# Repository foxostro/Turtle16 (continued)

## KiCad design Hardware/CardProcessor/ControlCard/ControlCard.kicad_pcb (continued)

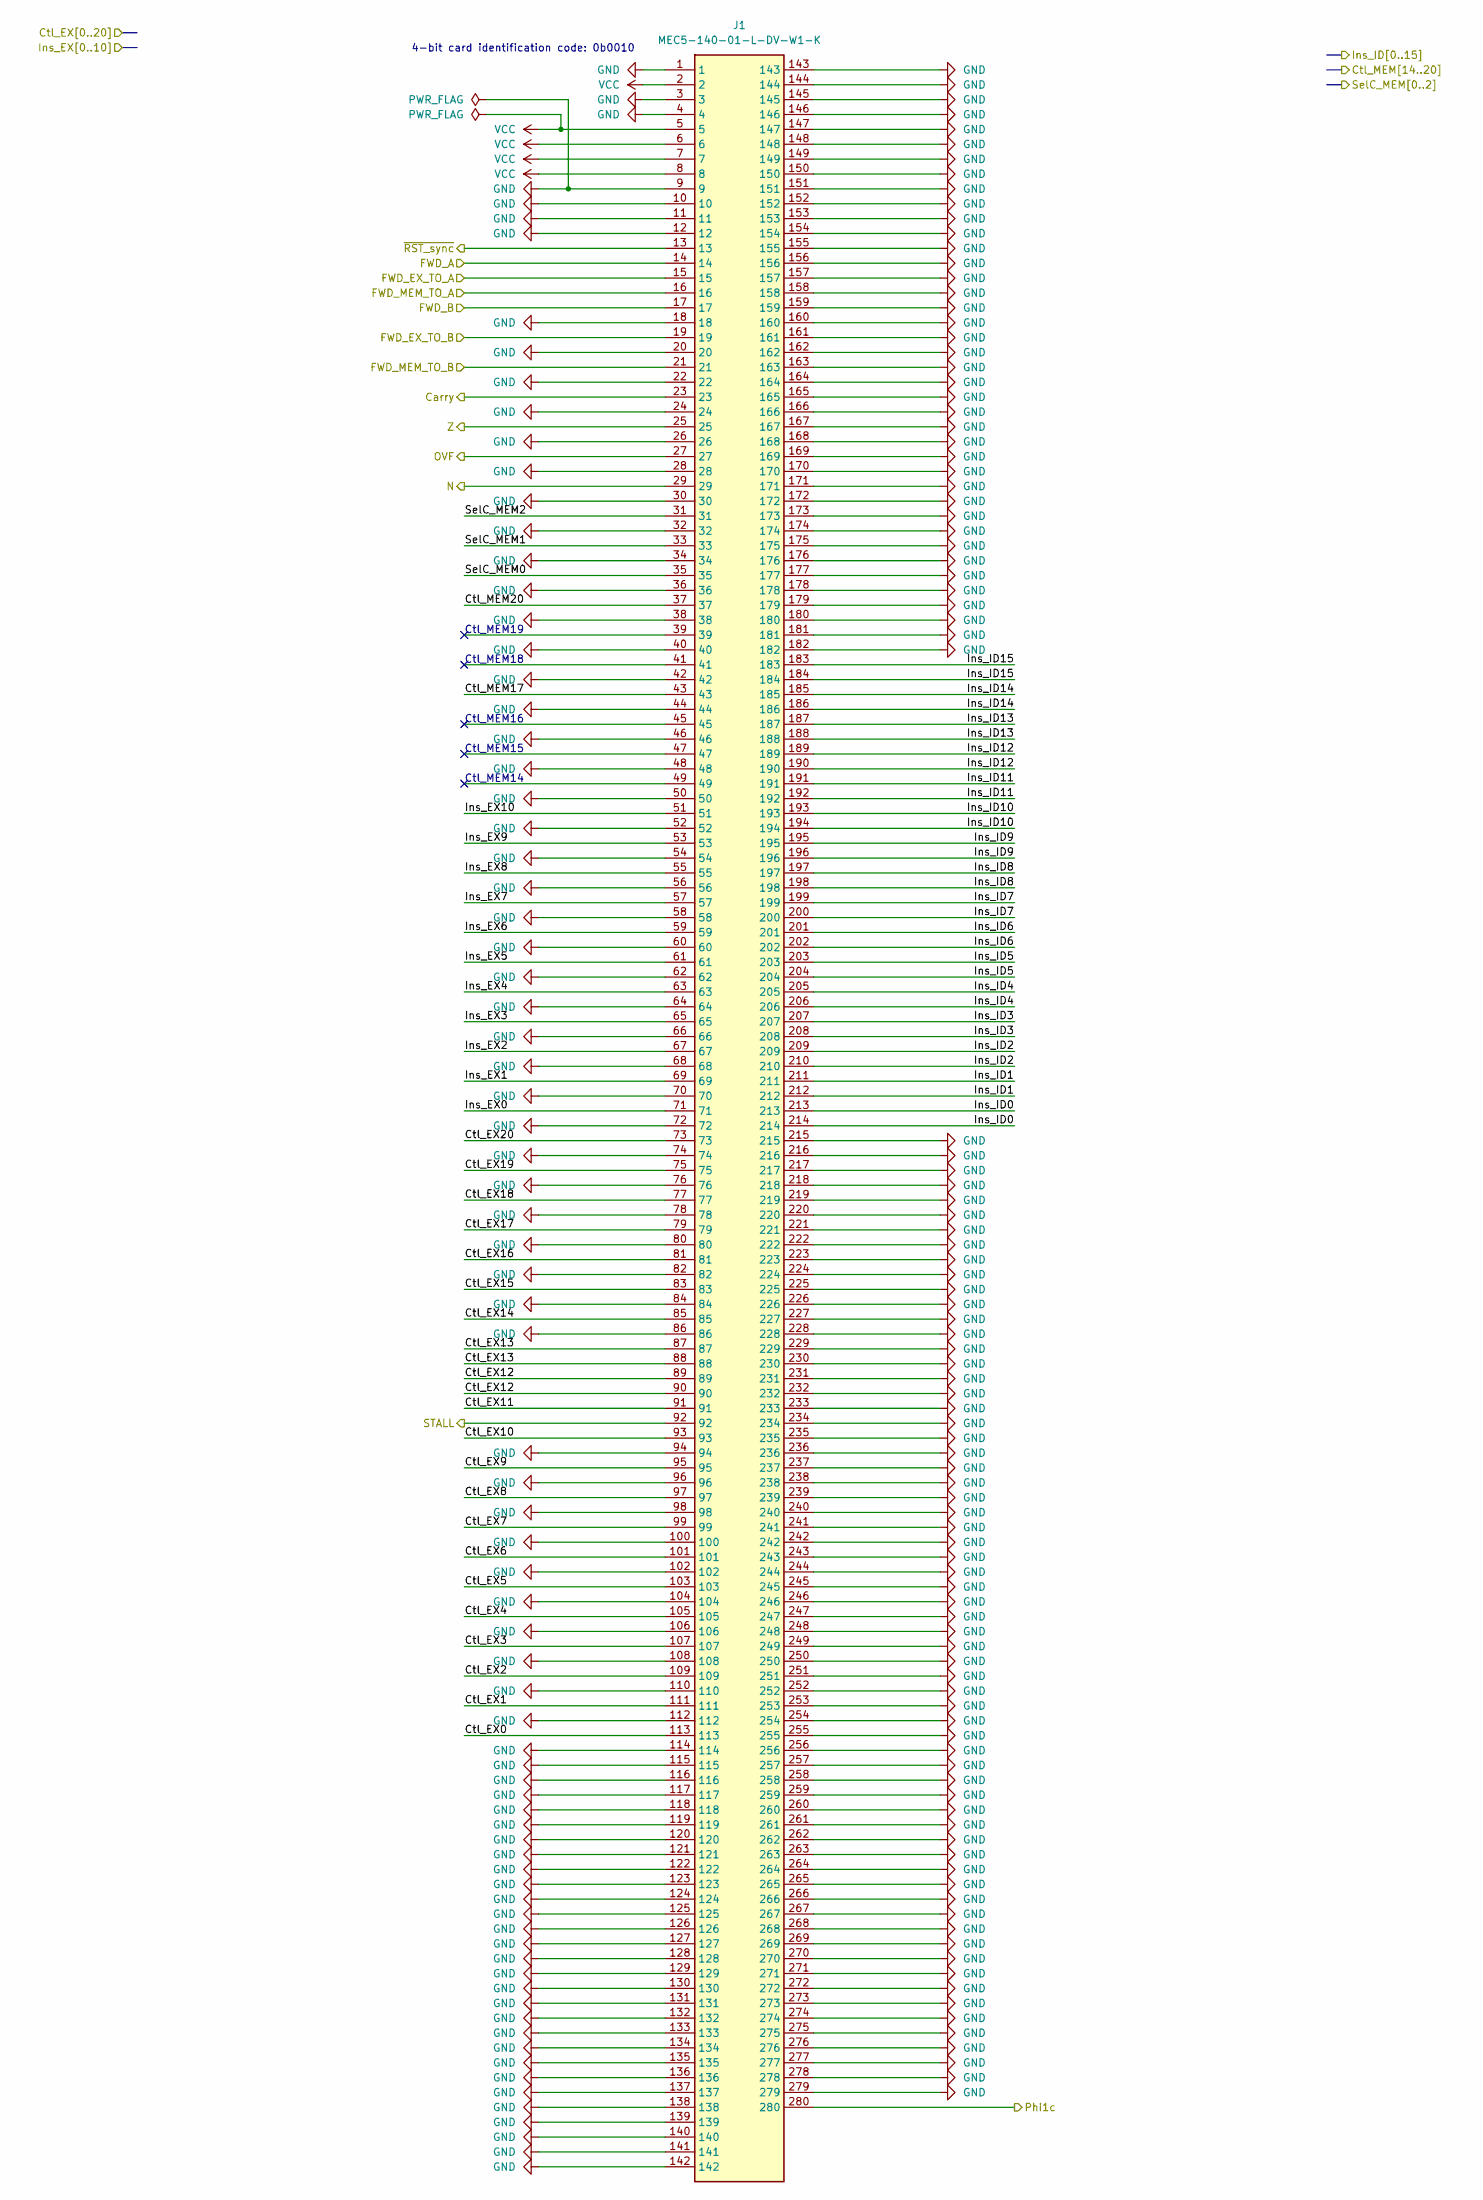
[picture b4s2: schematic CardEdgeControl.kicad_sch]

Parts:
J1: MEC5-140-01-L-DV-W1-K; MEC5-140-01-L-DV-W1-K_Edge; Mouser Part Number 200-MEC514001LDVW1K

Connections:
/CardEdgeControl/Carry: J1.23; also elsewhere on the board
/CardEdgeControl/Ctl_MEM17: J1.43; also elsewhere on the board
/CardEdgeControl/Ctl_MEM20: J1.37; also elsewhere on the board
/CardEdgeControl/FWD_A: J1.14; also elsewhere on the board
/CardEdgeControl/FWD_B: J1.17; also elsewhere on the board
/CardEdgeControl/FWD_EX_TO_A: J1.15; also elsewhere on the board
/CardEdgeControl/FWD_EX_TO_B: J1.19; also elsewhere on the board
/CardEdgeControl/FWD_MEM_TO_A: J1.16; also elsewhere on the board
/CardEdgeControl/FWD_MEM_TO_B: J1.21; also elsewhere on the board
/CardEdgeControl/Ins_ID0: J1.213, J1.214; also elsewhere on the board
/CardEdgeControl/Ins_ID1: J1.211, J1.212; also elsewhere on the board
/CardEdgeControl/Ins_ID2: J1.209, J1.210; also elsewhere on the board
/CardEdgeControl/Ins_ID3: J1.207, J1.208; also elsewhere on the board
/CardEdgeControl/Ins_ID4: J1.205, J1.206; also elsewhere on the board
/CardEdgeControl/Ins_ID5: J1.203, J1.204; also elsewhere on the board
/CardEdgeControl/Ins_ID6: J1.201, J1.202; also elsewhere on the board
/CardEdgeControl/Ins_ID7: J1.199, J1.200; also elsewhere on the board
/CardEdgeControl/Ins_ID8: J1.197, J1.198; also elsewhere on the board
/CardEdgeControl/Ins_ID9: J1.195, J1.196; also elsewhere on the board
/CardEdgeControl/Ins_ID10: J1.193, J1.194; also elsewhere on the board
/CardEdgeControl/Ins_ID11: J1.191, J1.192; also elsewhere on the board
/CardEdgeControl/Ins_ID12: J1.189, J1.190; also elsewhere on the board
/CardEdgeControl/Ins_ID13: J1.187, J1.188; also elsewhere on the board
/CardEdgeControl/Ins_ID14: J1.185, J1.186; also elsewhere on the board
/CardEdgeControl/Ins_ID15: J1.183, J1.184; also elsewhere on the board
/CardEdgeControl/N: J1.29; also elsewhere on the board
/CardEdgeControl/OVF: J1.27; also elsewhere on the board
/CardEdgeControl/Phi1c: J1.280; also elsewhere on the board
/CardEdgeControl/SelC_MEM0: J1.35; also elsewhere on the board
/CardEdgeControl/SelC_MEM1: J1.33; also elsewhere on the board
/CardEdgeControl/SelC_MEM2: J1.31; also elsewhere on the board
/CardEdgeControl/Z: J1.25; also elsewhere on the board
/CardEdgeControl/~RST_sync: J1.13; also elsewhere on the board
/ID/Ctl_EX0: J1.113; also elsewhere on the board
/ID/Ctl_EX1: J1.111; also elsewhere on the board
/ID/Ctl_EX2: J1.109; also elsewhere on the board
/ID/Ctl_EX3: J1.107; also elsewhere on the board
/ID/Ctl_EX4: J1.105; also elsewhere on the board
/ID/Ctl_EX5: J1.103; also elsewhere on the board
/ID/Ctl_EX6: J1.101; also elsewhere on the board
/ID/Ctl_EX7: J1.99; also elsewhere on the board
/ID/Ctl_EX8: J1.97; also elsewhere on the board
/ID/Ctl_EX9: J1.95; also elsewhere on the board
/ID/Ctl_EX10: J1.93; also elsewhere on the board
/ID/Ctl_EX11: J1.91; also elsewhere on the board
/ID/Ctl_EX12: J1.89, J1.90; also elsewhere on the board
/ID/Ctl_EX13: J1.87, J1.88; also elsewhere on the board
/ID/Ctl_EX14: J1.85; also elsewhere on the board
/ID/Ctl_EX15: J1.83; also elsewhere on the board
/ID/Ctl_EX16: J1.81; also elsewhere on the board
/ID/Ctl_EX17: J1.79; also elsewhere on the board
/ID/Ctl_EX18: J1.77; also elsewhere on the board
/ID/Ctl_EX19: J1.75; also elsewhere on the board
/ID/Ctl_EX20: J1.73; also elsewhere on the board
/ID/Hazard Control/STALL: J1.92; also elsewhere on the board
/ID/Ins_EX0: J1.71; also elsewhere on the board
/ID/Ins_EX1: J1.69; also elsewhere on the board
/ID/Ins_EX2: J1.67; also elsewhere on the board
/ID/Ins_EX3: J1.65; also elsewhere on the board
/ID/Ins_EX4: J1.63; also elsewhere on the board
/ID/Ins_EX5: J1.61; also elsewhere on the board
/ID/Ins_EX6: J1.59; also elsewhere on the board
/ID/Ins_EX7: J1.57; also elsewhere on the board
/ID/Ins_EX8: J1.55; also elsewhere on the board
/ID/Ins_EX9: J1.53; also elsewhere on the board
/ID/Ins_EX10: J1.51; also elsewhere on the board
GND: J1.1, J1.3, J1.4, J1.9, J1.10, J1.11, J1.12, J1.18, J1.20, J1.22, J1.24, J1.26, J1.28, J1.30, J1.32, J1.34, J1.36, J1.38, J1.40, J1.42, J1.44, J1.46, J1.48, J1.50, J1.52, J1.54, J1.56, J1.58, J1.60, J1.62, J1.64, J1.66, J1.68, J1.70, J1.72, J1.74, J1.76, J1.78, J1.80, J1.82, J1.84, J1.86, J1.94, J1.96, J1.98, J1.100, J1.102, J1.104, J1.106, J1.108, J1.110, J1.112, J1.114, J1.115, J1.116, J1.117, J1.118, J1.119, J1.120, J1.121, J1.122, J1.123, J1.124, J1.125, J1.126, J1.127, J1.128, J1.129, J1.130, J1.131, J1.132, J1.133, J1.134, J1.135, J1.136, J1.137, J1.138, J1.139, J1.140, J1.141, J1.142, J1.143, J1.144, J1.145, J1.146, J1.147, J1.148, J1.149, J1.150, J1.151, J1.152, J1.153, J1.154, J1.155, J1.156, J1.157, J1.158, J1.159, J1.160, J1.161, J1.162, J1.163, J1.164, J1.165, J1.166, J1.167, J1.168, J1.169, J1.170, J1.171, J1.172, J1.173, J1.174, J1.175, J1.176, J1.177, J1.178, J1.179, J1.180, J1.181, J1.182, J1.215, J1.216, J1.217, J1.218, J1.219, J1.220, J1.221, J1.222, J1.223, J1.224, J1.225, J1.226, J1.227, J1.228, J1.229, J1.230, J1.231, J1.232, J1.233, J1.234, J1.235, J1.236, J1.237, J1.238, J1.239, J1.240, J1.241, J1.242, J1.243, J1.244, J1.245, J1.246, J1.247, J1.248, J1.249, J1.250, J1.251, J1.252, J1.253, J1.254, J1.255, J1.256, J1.257, J1.258, J1.259, J1.260, J1.261, J1.262, J1.263, J1.264, J1.265, J1.266, J1.267, J1.268, J1.269, J1.270, J1.271, J1.272, J1.273, J1.274, J1.275, J1.276, J1.277, J1.278, J1.279; also elsewhere on the board
VCC: J1.2, J1.5, J1.6, J1.7, J1.8; also elsewhere on the board

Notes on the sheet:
Ctl_MEM16
4-bit card identification code: 0b0010
Ctl_MEM15
Ctl_MEM19
Ctl_MEM18
Ctl_MEM14

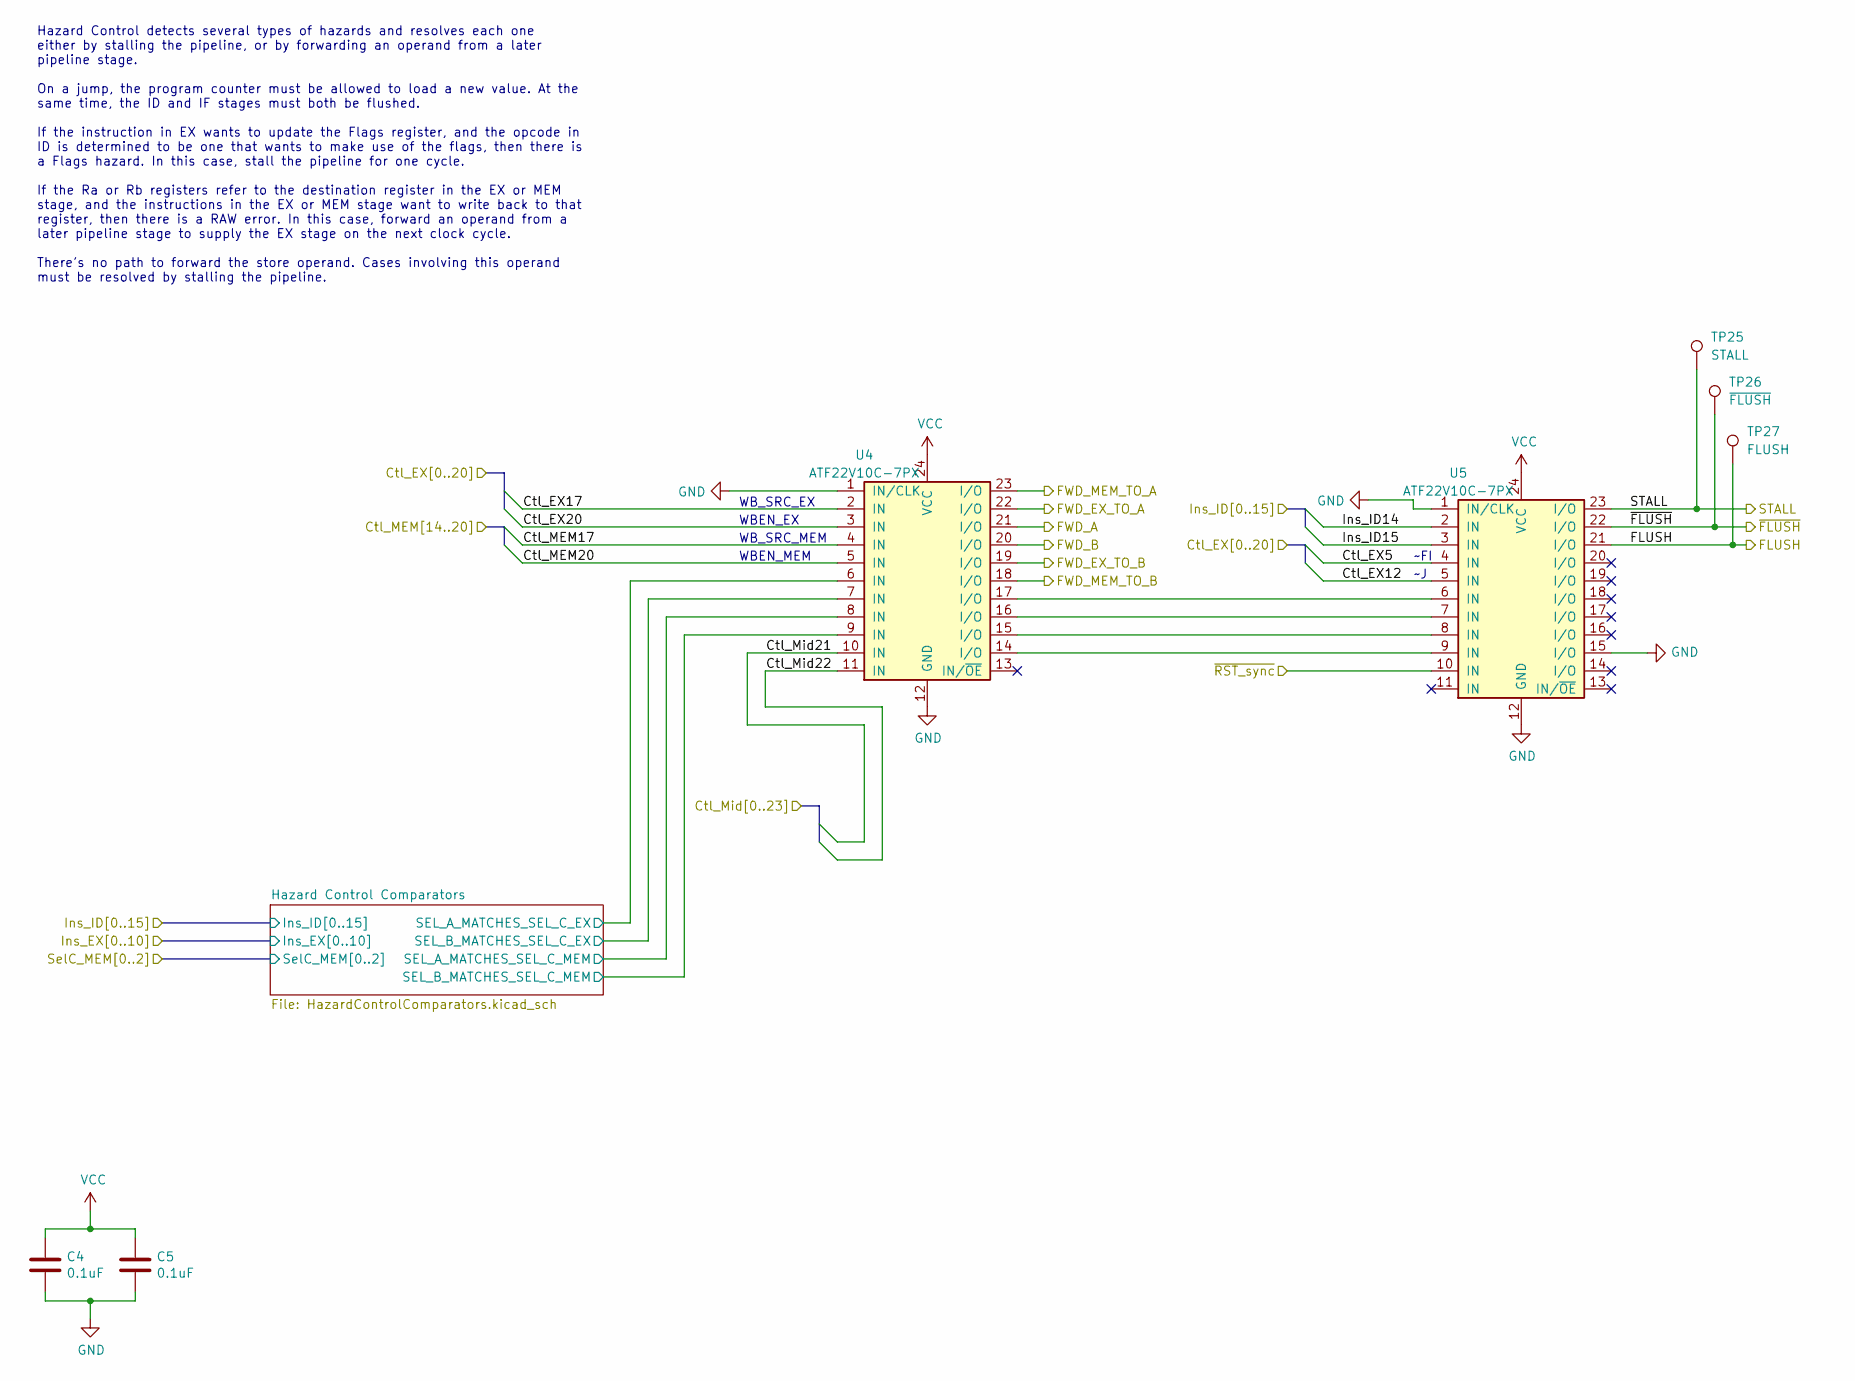
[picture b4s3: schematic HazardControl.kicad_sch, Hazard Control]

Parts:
C4, C5: 0.1uF; C_0603_1608Metric; Manufacturer# EMK107B7104KAHT; Mouser# 963-EMK107B7104KAHT
TP25: STALL; TestPoint_Pad_D1.0mm
TP26: ~{FLUSH}; TestPoint_Pad_D1.0mm
TP27: FLUSH; TestPoint_Pad_D1.0mm
U4, U5: ATF22V10C-7PX; DIP-24_W7.62mm_Socket; Manufacturer# ATF22V10C-7PX; Mouser# 556-AF22V10C7PX

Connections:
/CardEdgeControl/Ctl_MEM17: U4.4 (IN); also elsewhere on the board
/CardEdgeControl/Ctl_MEM20: U4.5 (IN); also elsewhere on the board
/CardEdgeControl/FWD_A: U4.21 (I/O); also elsewhere on the board
/CardEdgeControl/FWD_B: U4.20 (I/O); also elsewhere on the board
/CardEdgeControl/FWD_EX_TO_A: U4.22 (I/O); also elsewhere on the board
/CardEdgeControl/FWD_EX_TO_B: U4.19 (I/O); also elsewhere on the board
/CardEdgeControl/FWD_MEM_TO_A: U4.23 (I/O); also elsewhere on the board
/CardEdgeControl/FWD_MEM_TO_B: U4.18 (I/O); also elsewhere on the board
/CardEdgeControl/Ins_ID14: U5.2 (IN); also elsewhere on the board
/CardEdgeControl/Ins_ID15: U5.3 (IN); also elsewhere on the board
/CardEdgeControl/~RST_sync: U5.10 (IN); also elsewhere on the board
/ID/Ctl_EX5: U5.4 (IN); also elsewhere on the board
/ID/Ctl_EX12: U5.5 (IN); also elsewhere on the board
/ID/Ctl_EX17: U4.2 (IN); also elsewhere on the board
/ID/Ctl_EX20: U4.3 (IN); also elsewhere on the board
/ID/Ctl_Mid21: U4.10 (IN); also elsewhere on the board
/ID/Ctl_Mid22: U4.11 (IN); also elsewhere on the board
/ID/Hazard Control/FLUSH: TP27.1, U5.21 (I/O); also elsewhere on the board
/ID/Hazard Control/Hazard Control Comparators/SEL_A_MATCHES_SEL_C_EX: U4.6 (IN); also elsewhere on the board
/ID/Hazard Control/Hazard Control Comparators/SEL_A_MATCHES_SEL_C_MEM: U4.8 (IN); also elsewhere on the board
/ID/Hazard Control/Hazard Control Comparators/SEL_B_MATCHES_SEL_C_EX: U4.7 (IN); also elsewhere on the board
/ID/Hazard Control/Hazard Control Comparators/SEL_B_MATCHES_SEL_C_MEM: U4.9 (IN); also elsewhere on the board
/ID/Hazard Control/STALL: TP25.1, U5.23 (I/O); also elsewhere on the board
/ID/Hazard Control/~FLUSH: TP26.1, U5.22 (I/O); also elsewhere on the board
GND: C4.2, C5.2, U4.1 (IN/CLK), U4.12 (GND), U5.1 (IN/CLK), U5.12 (GND), U5.15 (I/O); also elsewhere on the board
unnamed: U4.14 (I/O), U5.9 (IN)
unnamed: U4.15 (I/O), U5.8 (IN)
unnamed: U4.16 (I/O), U5.7 (IN)
unnamed: U4.17 (I/O), U5.6 (IN)
VCC: C4.1, C5.1, U4.24 (VCC), U5.24 (VCC); also elsewhere on the board

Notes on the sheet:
Hazard Control detects several types of hazards and resolves each one either by stalling the pipeline, or by forwarding an operand from a later pipeline stage. On a jump, the program counter must be allowed to load a new value. At the same time, the ID and IF stages must both be flushed. If the ins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
WBEN_EX
WBEN_MEM
WB_SRC_EX
~FI
WB_SRC_MEM

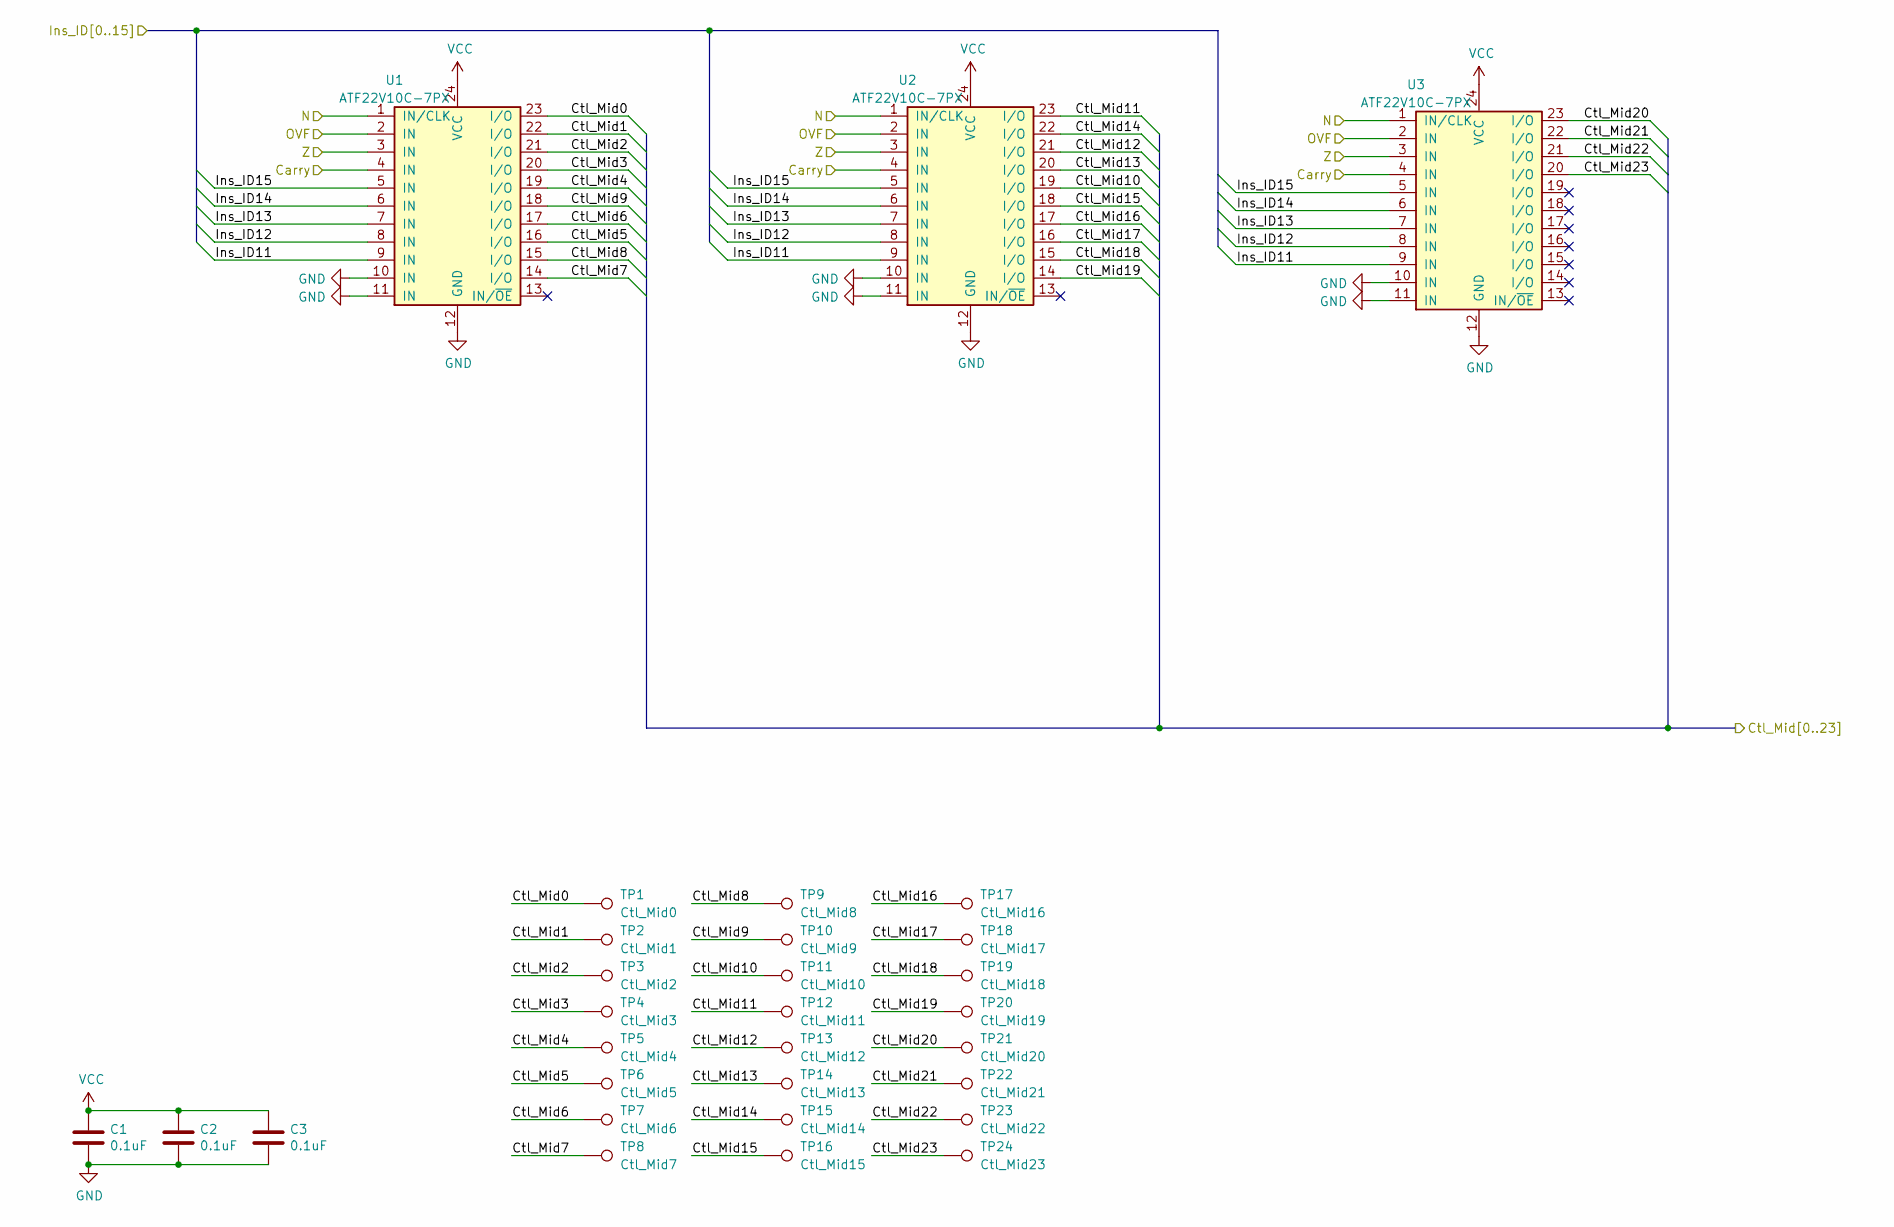
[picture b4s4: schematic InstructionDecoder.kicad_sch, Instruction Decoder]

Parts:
C1, C2, C3: 0.1uF; C_0603_1608Metric; Manufacturer# EMK107B7104KAHT; Mouser# 963-EMK107B7104KAHT
TP1: Ctl_Mid0; TestPoint_Pad_D1.0mm
TP2: Ctl_Mid1; TestPoint_Pad_D1.0mm
TP3: Ctl_Mid2; TestPoint_Pad_D1.0mm
TP4: Ctl_Mid3; TestPoint_Pad_D1.0mm
TP5: Ctl_Mid4; TestPoint_Pad_D1.0mm
TP6: Ctl_Mid5; TestPoint_Pad_D1.0mm
TP7: Ctl_Mid6; TestPoint_Pad_D1.0mm
TP8: Ctl_Mid7; TestPoint_Pad_D1.0mm
TP9: Ctl_Mid8; TestPoint_Pad_D1.0mm
TP10: Ctl_Mid9; TestPoint_Pad_D1.0mm
TP11: Ctl_Mid10; TestPoint_Pad_D1.0mm
TP12: Ctl_Mid11; TestPoint_Pad_D1.0mm
TP13: Ctl_Mid12; TestPoint_Pad_D1.0mm
TP14: Ctl_Mid13; TestPoint_Pad_D1.0mm
TP15: Ctl_Mid14; TestPoint_Pad_D1.0mm
TP16: Ctl_Mid15; TestPoint_Pad_D1.0mm
TP17: Ctl_Mid16; TestPoint_Pad_D1.0mm
TP18: Ctl_Mid17; TestPoint_Pad_D1.0mm
TP19: Ctl_Mid18; TestPoint_Pad_D1.0mm
TP20: Ctl_Mid19; TestPoint_Pad_D1.0mm
TP21: Ctl_Mid20; TestPoint_Pad_D1.0mm
TP22: Ctl_Mid21; TestPoint_Pad_D1.0mm
TP23: Ctl_Mid22; TestPoint_Pad_D1.0mm
TP24: Ctl_Mid23; TestPoint_Pad_D1.0mm
U1, U2, U3: ATF22V10C-7PX; DIP-24_W7.62mm_Socket; Manufacturer# ATF22V10C-7PX; Mouser# 556-AF22V10C7PX

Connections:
/CardEdgeControl/Carry: U1.4 (IN), U2.4 (IN), U3.4 (IN); also elsewhere on the board
/CardEdgeControl/Ins_ID11: U1.9 (IN), U2.9 (IN), U3.9 (IN); also elsewhere on the board
/CardEdgeControl/Ins_ID12: U1.8 (IN), U2.8 (IN), U3.8 (IN); also elsewhere on the board
/CardEdgeControl/Ins_ID13: U1.7 (IN), U2.7 (IN), U3.7 (IN); also elsewhere on the board
/CardEdgeControl/Ins_ID14: U1.6 (IN), U2.6 (IN), U3.6 (IN); also elsewhere on the board
/CardEdgeControl/Ins_ID15: U1.5 (IN), U2.5 (IN), U3.5 (IN); also elsewhere on the board
/CardEdgeControl/N: U1.1 (IN/CLK), U2.1 (IN/CLK), U3.1 (IN/CLK); also elsewhere on the board
/CardEdgeControl/OVF: U1.2 (IN), U2.2 (IN), U3.2 (IN); also elsewhere on the board
/CardEdgeControl/Z: U1.3 (IN), U2.3 (IN), U3.3 (IN); also elsewhere on the board
/ID/Ctl_Mid0: TP1.1, U1.23 (I/O); also elsewhere on the board
/ID/Ctl_Mid1: TP2.1, U1.22 (I/O); also elsewhere on the board
/ID/Ctl_Mid2: TP3.1, U1.21 (I/O); also elsewhere on the board
/ID/Ctl_Mid3: TP4.1, U1.20 (I/O); also elsewhere on the board
/ID/Ctl_Mid4: TP5.1, U1.19 (I/O); also elsewhere on the board
/ID/Ctl_Mid5: TP6.1, U1.16 (I/O); also elsewhere on the board
/ID/Ctl_Mid6: TP7.1, U1.17 (I/O); also elsewhere on the board
/ID/Ctl_Mid7: TP8.1, U1.14 (I/O); also elsewhere on the board
/ID/Ctl_Mid8: TP9.1, U1.15 (I/O); also elsewhere on the board
/ID/Ctl_Mid9: TP10.1, U1.18 (I/O); also elsewhere on the board
/ID/Ctl_Mid10: TP11.1, U2.19 (I/O); also elsewhere on the board
/ID/Ctl_Mid11: TP12.1, U2.23 (I/O); also elsewhere on the board
/ID/Ctl_Mid12: TP13.1, U2.21 (I/O); also elsewhere on the board
/ID/Ctl_Mid13: TP14.1, U2.20 (I/O); also elsewhere on the board
/ID/Ctl_Mid14: TP15.1, U2.22 (I/O); also elsewhere on the board
/ID/Ctl_Mid15: TP16.1, U2.18 (I/O); also elsewhere on the board
/ID/Ctl_Mid16: TP17.1, U2.17 (I/O); also elsewhere on the board
/ID/Ctl_Mid17: TP18.1, U2.16 (I/O); also elsewhere on the board
/ID/Ctl_Mid18: TP19.1, U2.15 (I/O); also elsewhere on the board
/ID/Ctl_Mid19: TP20.1, U2.14 (I/O); also elsewhere on the board
/ID/Ctl_Mid20: TP21.1, U3.23 (I/O); also elsewhere on the board
/ID/Ctl_Mid21: TP22.1, U3.22 (I/O); also elsewhere on the board
/ID/Ctl_Mid22: TP23.1, U3.21 (I/O); also elsewhere on the board
/ID/Ctl_Mid23: TP24.1, U3.20 (I/O); also elsewhere on the board
GND: C1.2, C2.2, C3.2, U1.10 (IN), U1.11 (IN), U1.12 (GND), U2.10 (IN), U2.11 (IN), U2.12 (GND), U3.10 (IN), U3.11 (IN), U3.12 (GND); also elsewhere on the board
VCC: C1.1, C2.1, C3.1, U1.24 (VCC), U2.24 (VCC), U3.24 (VCC); also elsewhere on the board

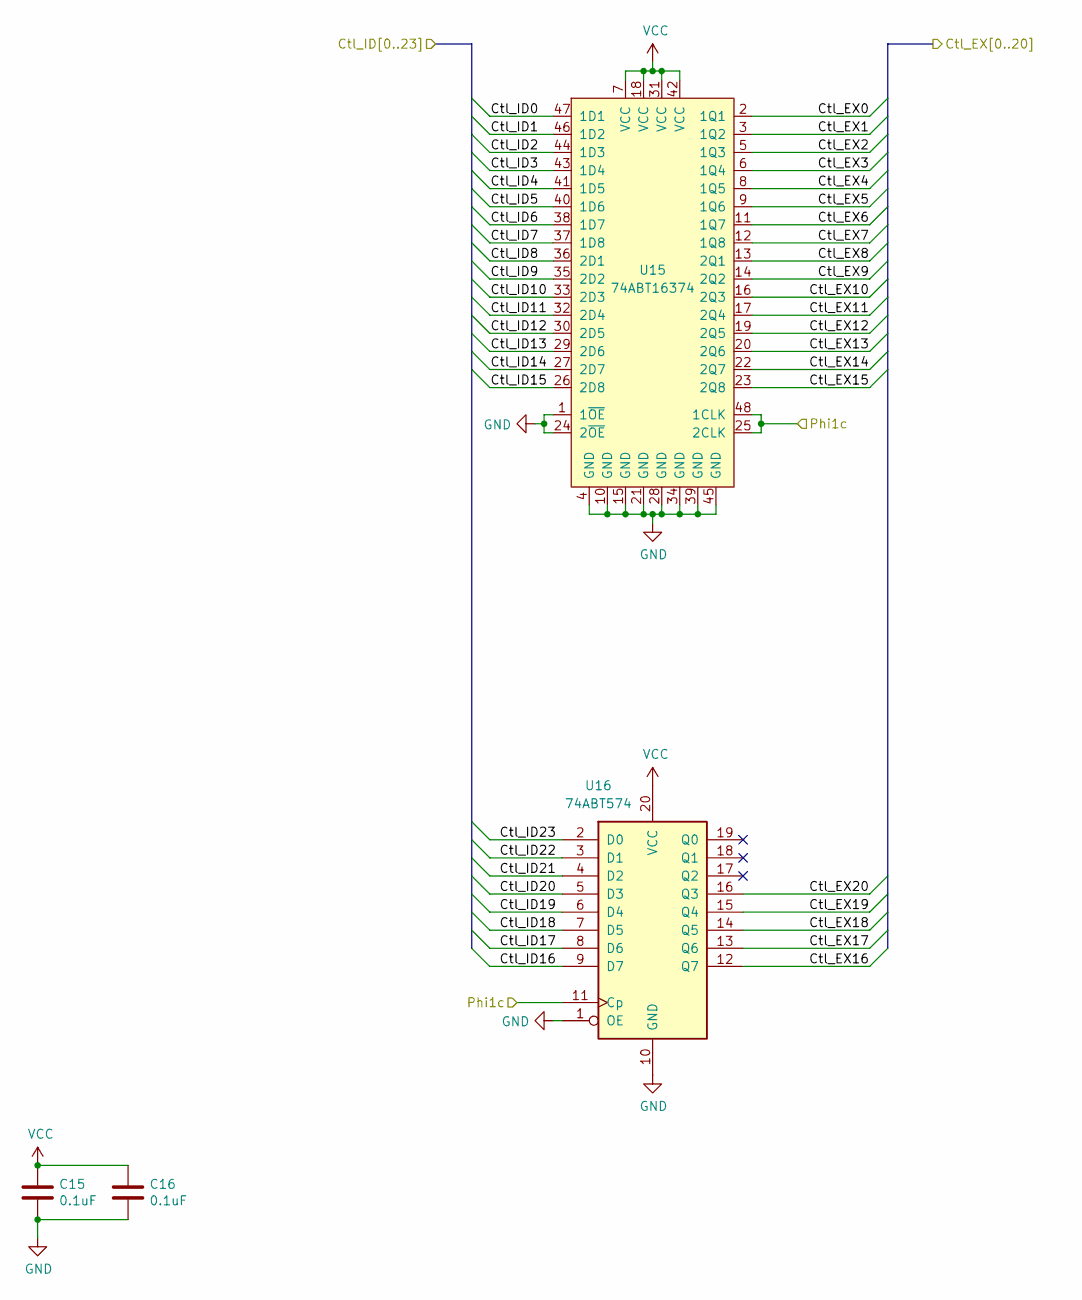
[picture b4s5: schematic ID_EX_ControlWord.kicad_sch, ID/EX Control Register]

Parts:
C15, C16: 0.1uF; C_0603_1608Metric; Manufacturer# EMK107B7104KAHT; Mouser# 963-EMK107B7104KAHT
U15: 74ABT16374; TSSOP-48_6.1x12.5mm_P0.5mm; Manufacturer# SN74ABT16374ADGGR; Mouser# 595-SNABT16374ADGGR
U16: 74ABT574; TSSOP-20_4.4x6.5mm_P0.65mm; Manufacturer# SN74ABT574APW; Mouser# 595-SN74ABT574APW

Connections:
/CardEdgeControl/Phi1c: U15.25 (2CLK), U15.48 (1CLK), U16.11 (Cp); also elsewhere on the board
/ID/Ctl_EX0: U15.2 (1Q1); also elsewhere on the board
/ID/Ctl_EX1: U15.3 (1Q2); also elsewhere on the board
/ID/Ctl_EX2: U15.5 (1Q3); also elsewhere on the board
/ID/Ctl_EX3: U15.6 (1Q4); also elsewhere on the board
/ID/Ctl_EX4: U15.8 (1Q5); also elsewhere on the board
/ID/Ctl_EX5: U15.9 (1Q6); also elsewhere on the board
/ID/Ctl_EX6: U15.11 (1Q7); also elsewhere on the board
/ID/Ctl_EX7: U15.12 (1Q8); also elsewhere on the board
/ID/Ctl_EX8: U15.13 (2Q1); also elsewhere on the board
/ID/Ctl_EX9: U15.14 (2Q2); also elsewhere on the board
/ID/Ctl_EX10: U15.16 (2Q3); also elsewhere on the board
/ID/Ctl_EX11: U15.17 (2Q4); also elsewhere on the board
/ID/Ctl_EX12: U15.19 (2Q5); also elsewhere on the board
/ID/Ctl_EX13: U15.20 (2Q6); also elsewhere on the board
/ID/Ctl_EX14: U15.22 (2Q7); also elsewhere on the board
/ID/Ctl_EX15: U15.23 (2Q8); also elsewhere on the board
/ID/Ctl_EX16: U16.12 (Q7); also elsewhere on the board
/ID/Ctl_EX17: U16.13 (Q6); also elsewhere on the board
/ID/Ctl_EX18: U16.14 (Q5); also elsewhere on the board
/ID/Ctl_EX19: U16.15 (Q4); also elsewhere on the board
/ID/Ctl_EX20: U16.16 (Q3); also elsewhere on the board
/ID/ID Flush/Ctl_ID0: U15.47 (1D1); also elsewhere on the board
/ID/ID Flush/Ctl_ID1: U15.46 (1D2); also elsewhere on the board
/ID/ID Flush/Ctl_ID2: U15.44 (1D3); also elsewhere on the board
/ID/ID Flush/Ctl_ID3: U15.43 (1D4); also elsewhere on the board
/ID/ID Flush/Ctl_ID4: U15.41 (1D5); also elsewhere on the board
/ID/ID Flush/Ctl_ID5: U15.40 (1D6); also elsewhere on the board
/ID/ID Flush/Ctl_ID6: U15.38 (1D7); also elsewhere on the board
/ID/ID Flush/Ctl_ID7: U15.37 (1D8); also elsewhere on the board
/ID/ID Flush/Ctl_ID8: U15.36 (2D1); also elsewhere on the board
/ID/ID Flush/Ctl_ID9: U15.35 (2D2); also elsewhere on the board
/ID/ID Flush/Ctl_ID10: U15.33 (2D3); also elsewhere on the board
/ID/ID Flush/Ctl_ID11: U15.32 (2D4); also elsewhere on the board
/ID/ID Flush/Ctl_ID12: U15.30 (2D5); also elsewhere on the board
/ID/ID Flush/Ctl_ID13: U15.29 (2D6); also elsewhere on the board
/ID/ID Flush/Ctl_ID14: U15.27 (2D7); also elsewhere on the board
/ID/ID Flush/Ctl_ID15: U15.26 (2D8); also elsewhere on the board
/ID/ID Flush/Ctl_ID16: U16.9 (D7); also elsewhere on the board
/ID/ID Flush/Ctl_ID17: U16.8 (D6); also elsewhere on the board
/ID/ID Flush/Ctl_ID18: U16.7 (D5); also elsewhere on the board
/ID/ID Flush/Ctl_ID19: U16.6 (D4); also elsewhere on the board
/ID/ID Flush/Ctl_ID20: U16.5 (D3); also elsewhere on the board
/ID/ID Flush/Ctl_ID21: U16.4 (D2); also elsewhere on the board
/ID/ID Flush/Ctl_ID22: U16.3 (D1); also elsewhere on the board
/ID/ID Flush/Ctl_ID23: U16.2 (D0); also elsewhere on the board
GND: C15.2, C16.2, U15.1 (1~OE), U15.4 (GND), U15.10 (GND), U15.15 (GND), U15.21 (GND), U15.24 (2~OE), U15.28 (GND), U15.34 (GND), U15.39 (GND), U15.45 (GND), U16.1 (OE), U16.10 (GND); also elsewhere on the board
VCC: C15.1, C16.1, U15.7 (VCC), U15.18 (VCC), U15.31 (VCC), U15.42 (VCC), U16.20 (VCC); also elsewhere on the board

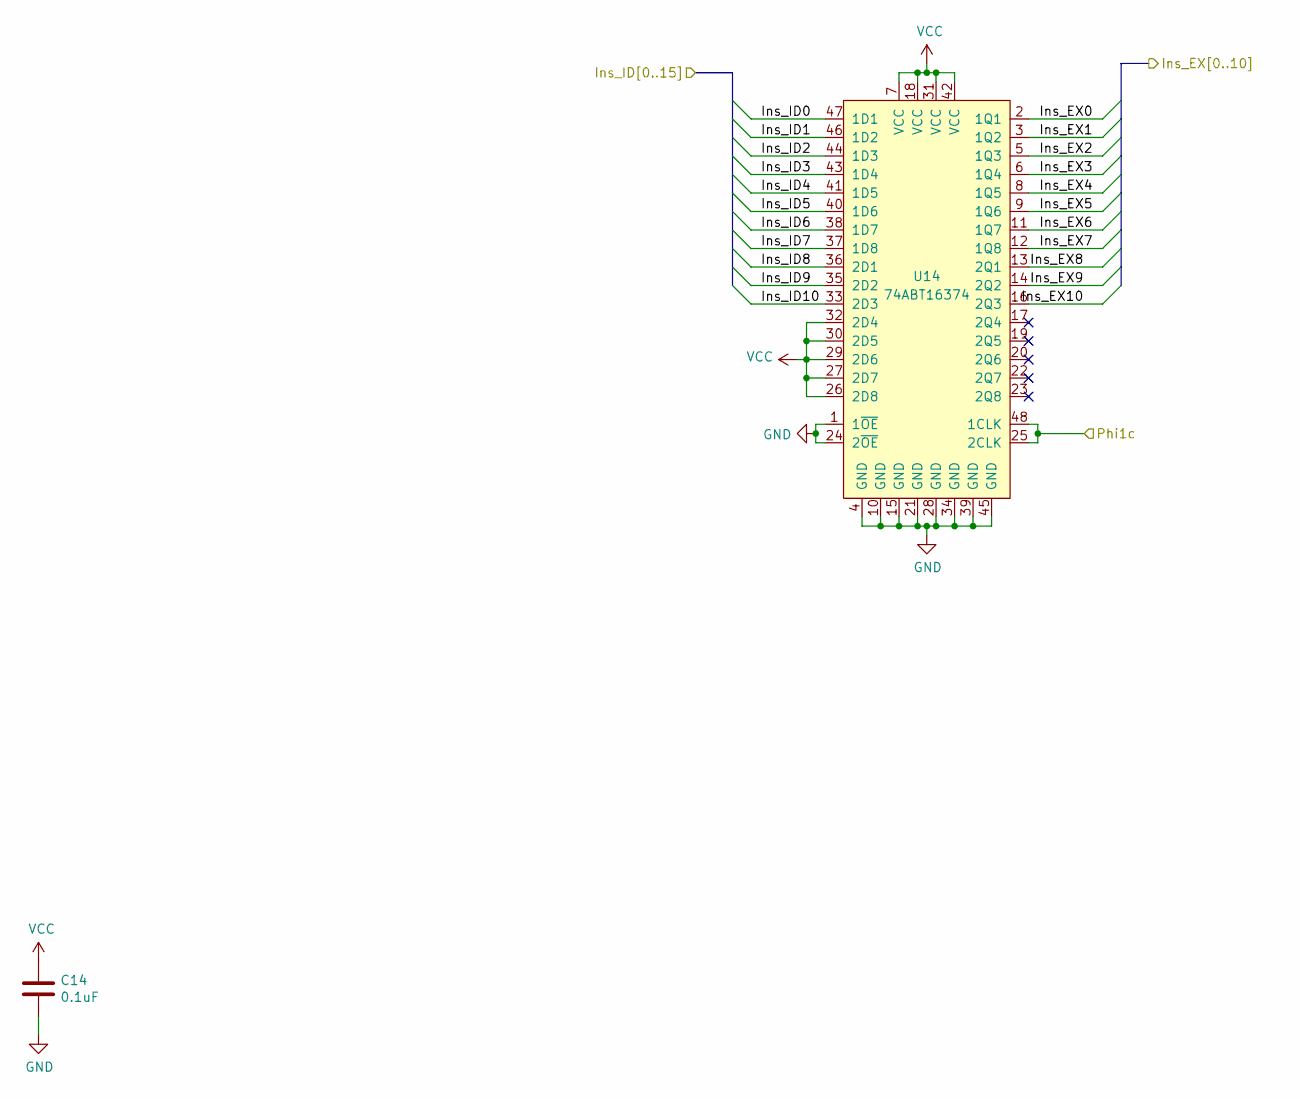
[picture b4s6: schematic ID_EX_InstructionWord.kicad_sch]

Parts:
C14: 0.1uF; C_0603_1608Metric; Manufacturer# EMK107B7104KAHT; Mouser# 963-EMK107B7104KAHT
U14: 74ABT16374; TSSOP-48_6.1x12.5mm_P0.5mm; Manufacturer# SN74ABT16374ADGGR; Mouser# 595-SNABT16374ADGGR

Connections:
/CardEdgeControl/Ins_ID0: U14.47 (1D1); also elsewhere on the board
/CardEdgeControl/Ins_ID1: U14.46 (1D2); also elsewhere on the board
/CardEdgeControl/Ins_ID2: U14.44 (1D3); also elsewhere on the board
/CardEdgeControl/Ins_ID3: U14.43 (1D4); also elsewhere on the board
/CardEdgeControl/Ins_ID4: U14.41 (1D5); also elsewhere on the board
/CardEdgeControl/Ins_ID5: U14.40 (1D6); also elsewhere on the board
/CardEdgeControl/Ins_ID6: U14.38 (1D7); also elsewhere on the board
/CardEdgeControl/Ins_ID7: U14.37 (1D8); also elsewhere on the board
/CardEdgeControl/Ins_ID8: U14.36 (2D1); also elsewhere on the board
/CardEdgeControl/Ins_ID9: U14.35 (2D2); also elsewhere on the board
/CardEdgeControl/Ins_ID10: U14.33 (2D3); also elsewhere on the board
/CardEdgeControl/Phi1c: U14.25 (2CLK), U14.48 (1CLK); also elsewhere on the board
/ID/Ins_EX0: U14.2 (1Q1); also elsewhere on the board
/ID/Ins_EX1: U14.3 (1Q2); also elsewhere on the board
/ID/Ins_EX2: U14.5 (1Q3); also elsewhere on the board
/ID/Ins_EX3: U14.6 (1Q4); also elsewhere on the board
/ID/Ins_EX4: U14.8 (1Q5); also elsewhere on the board
/ID/Ins_EX5: U14.9 (1Q6); also elsewhere on the board
/ID/Ins_EX6: U14.11 (1Q7); also elsewhere on the board
/ID/Ins_EX7: U14.12 (1Q8); also elsewhere on the board
/ID/Ins_EX8: U14.13 (2Q1); also elsewhere on the board
/ID/Ins_EX9: U14.14 (2Q2); also elsewhere on the board
/ID/Ins_EX10: U14.16 (2Q3); also elsewhere on the board
GND: C14.2, U14.1 (1~OE), U14.4 (GND), U14.10 (GND), U14.15 (GND), U14.21 (GND), U14.24 (2~OE), U14.28 (GND), U14.34 (GND), U14.39 (GND), U14.45 (GND); also elsewhere on the board
VCC: C14.1, U14.7 (VCC), U14.18 (VCC), U14.26 (2D8), U14.27 (2D7), U14.29 (2D6), U14.30 (2D5), U14.31 (VCC), U14.32 (2D4), U14.42 (VCC); also elsewhere on the board
